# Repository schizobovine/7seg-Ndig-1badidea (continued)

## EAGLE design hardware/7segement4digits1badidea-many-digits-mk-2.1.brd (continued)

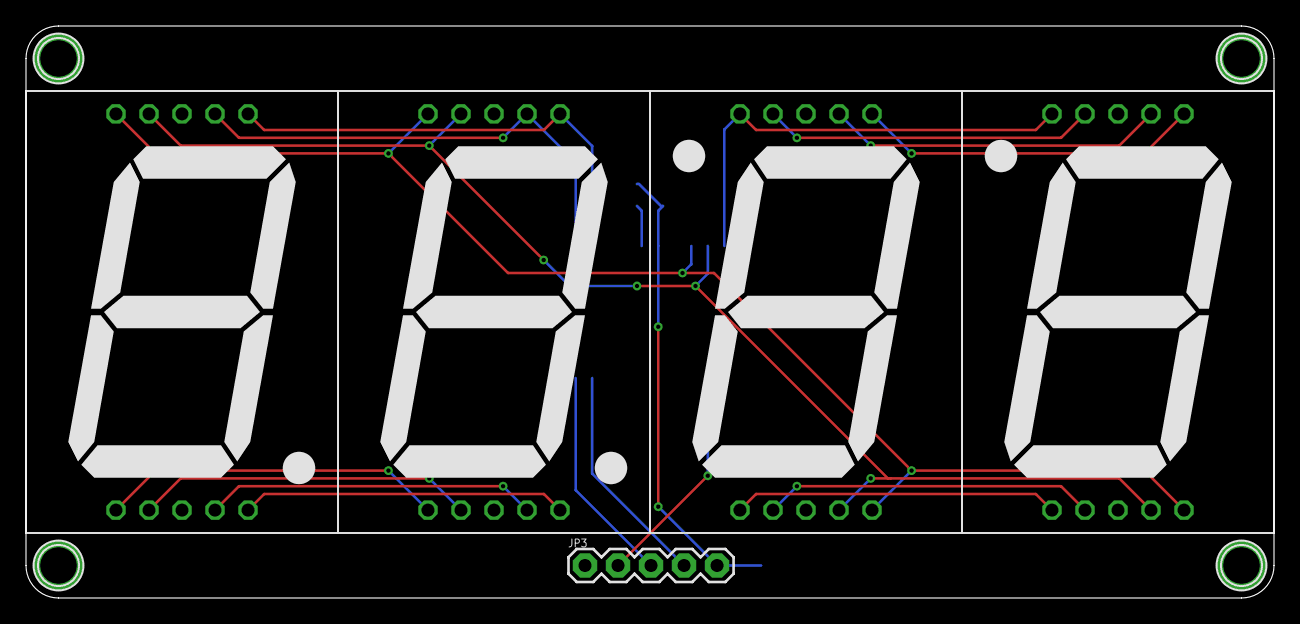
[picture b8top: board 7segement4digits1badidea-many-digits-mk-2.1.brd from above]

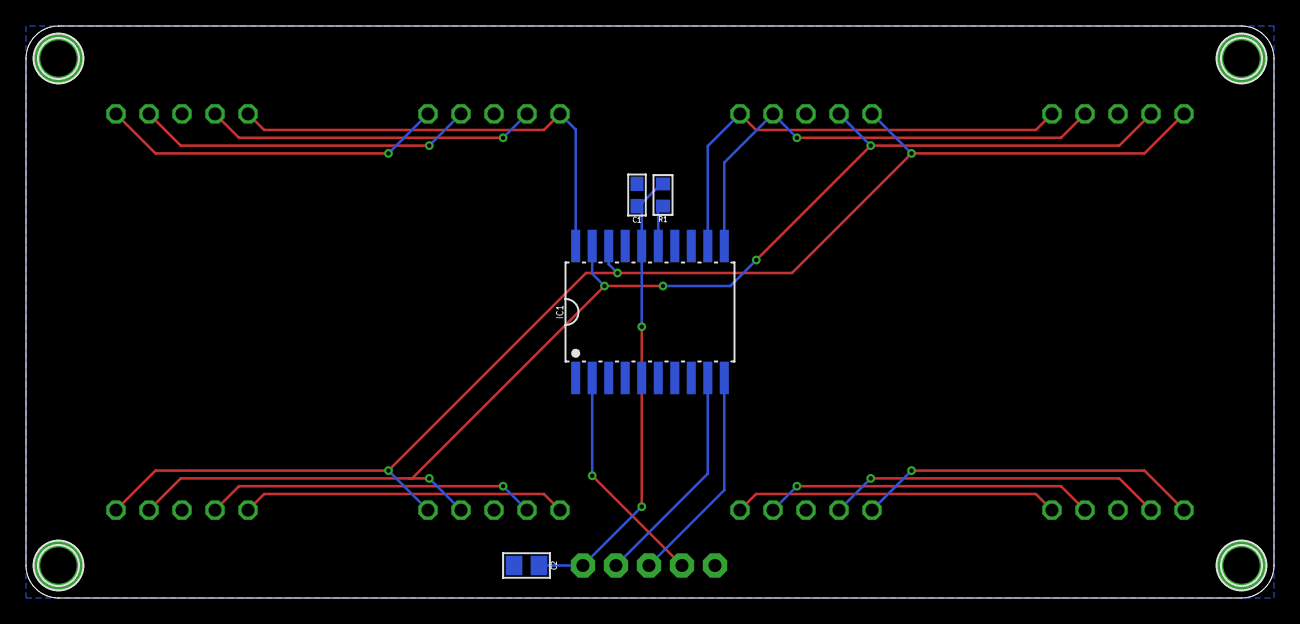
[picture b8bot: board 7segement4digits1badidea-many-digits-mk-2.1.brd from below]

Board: 2 copper layers, 96.0 x 44.0 mm, 13 parts (4 on the bottom side), 18 nets.
